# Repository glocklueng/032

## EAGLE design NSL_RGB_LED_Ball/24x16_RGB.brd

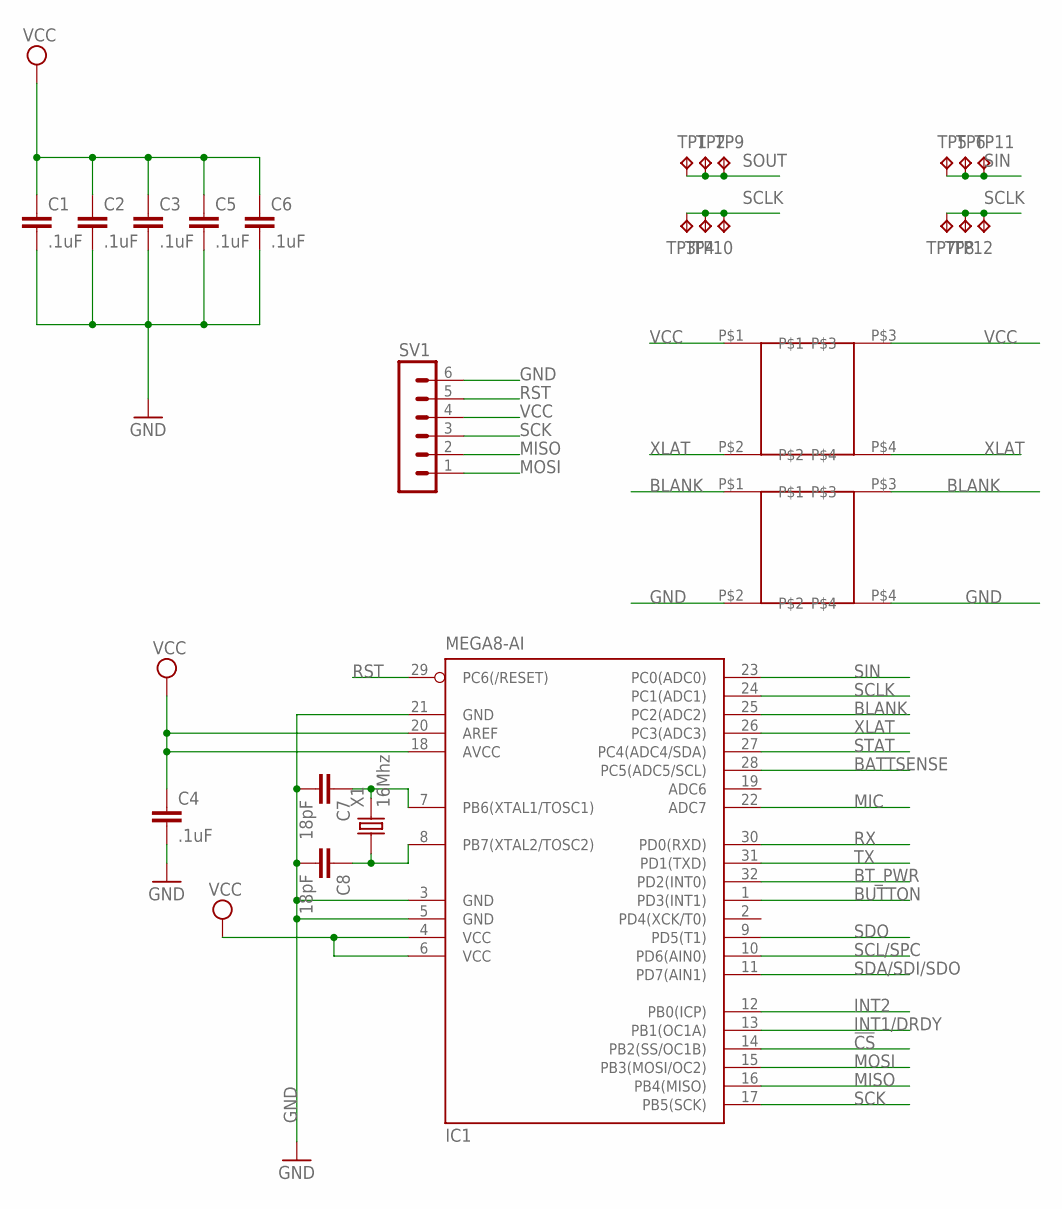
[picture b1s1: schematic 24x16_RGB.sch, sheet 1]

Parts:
C1, C2, C3, C4, C5, C6: .1uF; 0805
C7, C8: 18pF; 0805
IC1: MEGA8-AI; TQFP32-08
SLOT1, SLOT2: SLOT
SV1: MA06-1
TP1, TP2, TP3, TP4, TP5, TP6, TP7, TP8, TP9, TP10, TP11, TP12: TPTP20SQ; TP20SQ
X1: 16Mhz; 5032

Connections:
!CS: IC1.14 (PB2(SS/OC1B)); also elsewhere on the board
BATTSENSE: IC1.28 (PC5(ADC5/SCL)); also elsewhere on the board
BLANK: IC1.25 (PC2(ADC2)), SLOT2.P$1, SLOT2.P$3; also elsewhere on the board
BT_PWR: IC1.32 (PD2(INT0)); also elsewhere on the board
BUTTON: IC1.1 (PD3(INT1)); also elsewhere on the board
GND: C1.2, C2.2, C3.2, C4.2, C5.2, C6.2, C7.2, C8.2, IC1.3 (GND), IC1.5 (GND), IC1.21 (GND), SLOT2.P$2, SLOT2.P$4, SV1.6; also elsewhere on the board
INT1/DRDY: IC1.13 (PB1(OC1A)); also elsewhere on the board
INT2: IC1.12 (PB0(ICP)); also elsewhere on the board
MIC: IC1.22 (ADC7); also elsewhere on the board
MISO: IC1.16 (PB4(MISO)), SV1.2
MOSI: IC1.15 (PB3(MOSI/OC2)), SV1.1
unnamed: C7.1, IC1.7 (PB6(XTAL1/TOSC1)), X1.2
unnamed: C8.1, IC1.8 (PB7(XTAL2/TOSC2)), X1.1
RST: IC1.29 (PC6(/RESET)), SV1.5; also elsewhere on the board
RX: IC1.30 (PD0(RXD)); also elsewhere on the board
SCK: IC1.17 (PB5(SCK)), SV1.3
SCL/SPC: IC1.10 (PD6(AIN0)); also elsewhere on the board
SCLK: IC1.24 (PC1(ADC1)), TP3.TP, TP4.TP, TP7.TP, TP8.TP, TP10.TP, TP12.TP; also elsewhere on the board
SDA/SDI/SDO: IC1.11 (PD7(AIN1)); also elsewhere on the board
SDO: IC1.9 (PD5(T1)); also elsewhere on the board
SIN: IC1.23 (PC0(ADC0)), TP5.TP, TP6.TP, TP11.TP; also elsewhere on the board
SOUT: TP1.TP, TP2.TP, TP9.TP; also elsewhere on the board
STAT: IC1.27 (PC4(ADC4/SDA)); also elsewhere on the board
TX: IC1.31 (PD1(TXD)); also elsewhere on the board
VCC: C1.1, C2.1, C3.1, C4.1, C5.1, C6.1, IC1.4 (VCC), IC1.6 (VCC), IC1.18 (AVCC), IC1.20 (AREF), SLOT1.P$1, SLOT1.P$3, SV1.4; also elsewhere on the board
XLAT: IC1.26 (PC3(ADC3)), SLOT1.P$2, SLOT1.P$4; also elsewhere on the board

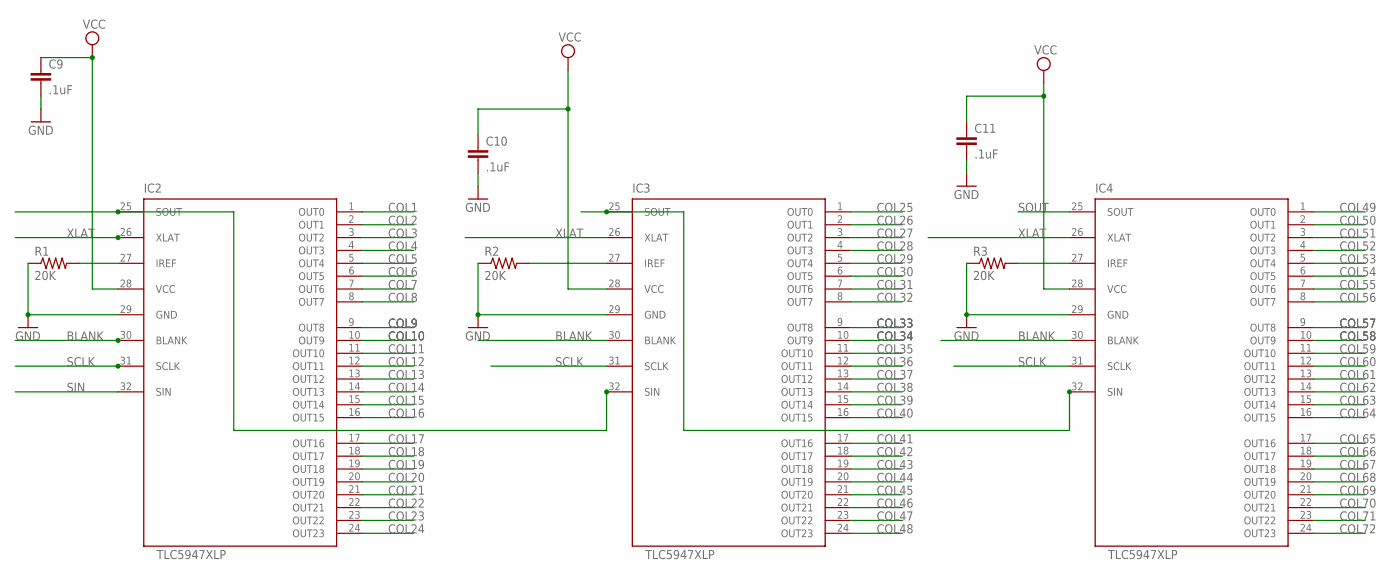
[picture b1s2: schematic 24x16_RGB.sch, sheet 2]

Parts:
C9, C10, C11: .1uF; 0805
IC2, IC3, IC4: TLC5947XLP; QFN32_XLP
R1, R2, R3: 20K; 0805

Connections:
BLANK: IC2.30 (BLANK), IC3.30 (BLANK), IC4.30 (BLANK); also elsewhere on the board
COL1: IC2.1 (OUT0); also elsewhere on the board
COL2: IC2.2 (OUT1); also elsewhere on the board
COL3: IC2.3 (OUT2); also elsewhere on the board
COL4: IC2.4 (OUT3); also elsewhere on the board
COL5: IC2.5 (OUT4); also elsewhere on the board
COL6: IC2.6 (OUT5); also elsewhere on the board
COL7: IC2.7 (OUT6); also elsewhere on the board
COL8: IC2.8 (OUT7); also elsewhere on the board
COL9: IC2.9 (OUT8); also elsewhere on the board
COL10: IC2.10 (OUT9); also elsewhere on the board
COL11: IC2.11 (OUT10); also elsewhere on the board
COL12: IC2.12 (OUT11); also elsewhere on the board
COL13: IC2.13 (OUT12); also elsewhere on the board
COL14: IC2.14 (OUT13); also elsewhere on the board
COL15: IC2.15 (OUT14); also elsewhere on the board
COL16: IC2.16 (OUT15); also elsewhere on the board
COL17: IC2.17 (OUT16); also elsewhere on the board
COL18: IC2.18 (OUT17); also elsewhere on the board
COL19: IC2.19 (OUT18); also elsewhere on the board
COL20: IC2.20 (OUT19); also elsewhere on the board
COL21: IC2.21 (OUT20); also elsewhere on the board
COL22: IC2.22 (OUT21); also elsewhere on the board
COL23: IC2.23 (OUT22); also elsewhere on the board
COL24: IC2.24 (OUT23); also elsewhere on the board
COL25: IC3.1 (OUT0); also elsewhere on the board
COL26: IC3.2 (OUT1); also elsewhere on the board
COL27: IC3.3 (OUT2); also elsewhere on the board
COL28: IC3.4 (OUT3); also elsewhere on the board
COL29: IC3.5 (OUT4); also elsewhere on the board
COL30: IC3.6 (OUT5); also elsewhere on the board
COL31: IC3.7 (OUT6); also elsewhere on the board
COL32: IC3.8 (OUT7); also elsewhere on the board
COL33: IC3.9 (OUT8); also elsewhere on the board
COL34: IC3.10 (OUT9); also elsewhere on the board
COL35: IC3.11 (OUT10); also elsewhere on the board
COL36: IC3.12 (OUT11); also elsewhere on the board
COL37: IC3.13 (OUT12); also elsewhere on the board
COL38: IC3.14 (OUT13); also elsewhere on the board
COL39: IC3.15 (OUT14); also elsewhere on the board
COL40: IC3.16 (OUT15); also elsewhere on the board
COL41: IC3.17 (OUT16); also elsewhere on the board
COL42: IC3.18 (OUT17); also elsewhere on the board
COL43: IC3.19 (OUT18); also elsewhere on the board
COL44: IC3.20 (OUT19); also elsewhere on the board
COL45: IC3.21 (OUT20); also elsewhere on the board
COL46: IC3.22 (OUT21); also elsewhere on the board
COL47: IC3.23 (OUT22); also elsewhere on the board
COL48: IC3.24 (OUT23); also elsewhere on the board
COL49: IC4.1 (OUT0); also elsewhere on the board
COL50: IC4.2 (OUT1); also elsewhere on the board
COL51: IC4.3 (OUT2); also elsewhere on the board
COL52: IC4.4 (OUT3); also elsewhere on the board
COL53: IC4.5 (OUT4); also elsewhere on the board
COL54: IC4.6 (OUT5); also elsewhere on the board
COL55: IC4.7 (OUT6); also elsewhere on the board
COL56: IC4.8 (OUT7); also elsewhere on the board
COL57: IC4.9 (OUT8); also elsewhere on the board
COL58: IC4.10 (OUT9); also elsewhere on the board
COL59: IC4.11 (OUT10); also elsewhere on the board
COL60: IC4.12 (OUT11); also elsewhere on the board
COL61: IC4.13 (OUT12); also elsewhere on the board
COL62: IC4.14 (OUT13); also elsewhere on the board
COL63: IC4.15 (OUT14); also elsewhere on the board
COL64: IC4.16 (OUT15); also elsewhere on the board
COL65: IC4.17 (OUT16); also elsewhere on the board
COL66: IC4.18 (OUT17); also elsewhere on the board
COL67: IC4.19 (OUT18); also elsewhere on the board
COL68: IC4.20 (OUT19); also elsewhere on the board
COL69: IC4.21 (OUT20); also elsewhere on the board
COL70: IC4.22 (OUT21); also elsewhere on the board
COL71: IC4.23 (OUT22); also elsewhere on the board
COL72: IC4.24 (OUT23); also elsewhere on the board
GND: C9.2, C10.2, C11.2, IC2.29 (GND), IC3.29 (GND), IC4.29 (GND), R1.1, R2.1, R3.1; also elsewhere on the board
HOLE: IC2.27 (IREF), R1.2
unnamed: IC3.27 (IREF), R2.2
unnamed: IC2.25 (SOUT), IC3.32 (SIN)
unnamed: IC4.27 (IREF), R3.2
unnamed: IC3.25 (SOUT), IC4.32 (SIN)
SCLK: IC2.31 (SCLK), IC3.31 (SCLK), IC4.31 (SCLK); also elsewhere on the board
SIN: IC2.32 (SIN); also elsewhere on the board
SOUT: IC4.25 (SOUT); also elsewhere on the board
VCC: C9.1, C10.1, C11.1, IC2.28 (VCC), IC3.28 (VCC), IC4.28 (VCC); also elsewhere on the board
XLAT: IC2.26 (XLAT), IC3.26 (XLAT), IC4.26 (XLAT); also elsewhere on the board

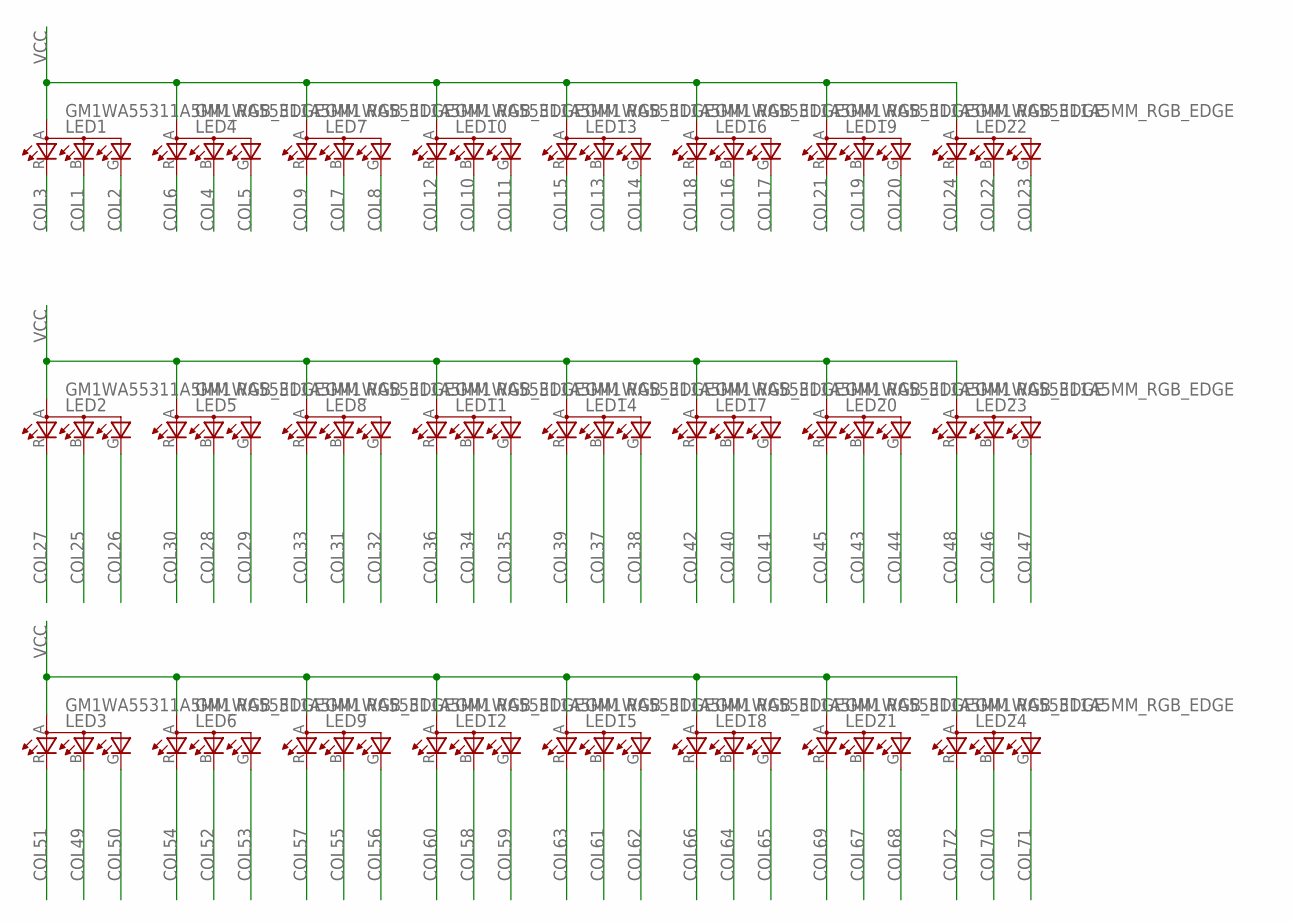
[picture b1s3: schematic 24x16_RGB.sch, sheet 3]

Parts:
LED1, LED2, LED3, LED4, LED5, LED6, LED7, LED8, LED9, LED10, LED11, LED12, LED13, LED14, LED15, LED16, LED17, LED18, LED19, LED20, LED21, LED22, LED23, LED24: GM1WA55311A5MM_RGB_EDGE; LED5MM_RGB_EDGE

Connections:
COL1: LED1.B (CBLUE); also elsewhere on the board
COL2: LED1.G (CGREEN); also elsewhere on the board
COL3: LED1.R (CRED); also elsewhere on the board
COL4: LED4.B (CBLUE); also elsewhere on the board
COL5: LED4.G (CGREEN); also elsewhere on the board
COL6: LED4.R (CRED); also elsewhere on the board
COL7: LED7.B (CBLUE); also elsewhere on the board
COL8: LED7.G (CGREEN); also elsewhere on the board
COL9: LED7.R (CRED); also elsewhere on the board
COL10: LED10.B (CBLUE); also elsewhere on the board
COL11: LED10.G (CGREEN); also elsewhere on the board
COL12: LED10.R (CRED); also elsewhere on the board
COL13: LED13.B (CBLUE); also elsewhere on the board
COL14: LED13.G (CGREEN); also elsewhere on the board
COL15: LED13.R (CRED); also elsewhere on the board
COL16: LED16.B (CBLUE); also elsewhere on the board
COL17: LED16.G (CGREEN); also elsewhere on the board
COL18: LED16.R (CRED); also elsewhere on the board
COL19: LED19.B (CBLUE); also elsewhere on the board
COL20: LED19.G (CGREEN); also elsewhere on the board
COL21: LED19.R (CRED); also elsewhere on the board
COL22: LED22.B (CBLUE); also elsewhere on the board
COL23: LED22.G (CGREEN); also elsewhere on the board
COL24: LED22.R (CRED); also elsewhere on the board
COL25: LED2.B (CBLUE); also elsewhere on the board
COL26: LED2.G (CGREEN); also elsewhere on the board
COL27: LED2.R (CRED); also elsewhere on the board
COL28: LED5.B (CBLUE); also elsewhere on the board
COL29: LED5.G (CGREEN); also elsewhere on the board
COL30: LED5.R (CRED); also elsewhere on the board
COL31: LED8.B (CBLUE); also elsewhere on the board
COL32: LED8.G (CGREEN); also elsewhere on the board
COL33: LED8.R (CRED); also elsewhere on the board
COL34: LED11.B (CBLUE); also elsewhere on the board
COL35: LED11.G (CGREEN); also elsewhere on the board
COL36: LED11.R (CRED); also elsewhere on the board
COL37: LED14.B (CBLUE); also elsewhere on the board
COL38: LED14.G (CGREEN); also elsewhere on the board
COL39: LED14.R (CRED); also elsewhere on the board
COL40: LED17.B (CBLUE); also elsewhere on the board
COL41: LED17.G (CGREEN); also elsewhere on the board
COL42: LED17.R (CRED); also elsewhere on the board
COL43: LED20.B (CBLUE); also elsewhere on the board
COL44: LED20.G (CGREEN); also elsewhere on the board
COL45: LED20.R (CRED); also elsewhere on the board
COL46: LED23.B (CBLUE); also elsewhere on the board
COL47: LED23.G (CGREEN); also elsewhere on the board
COL48: LED23.R (CRED); also elsewhere on the board
COL49: LED3.B (CBLUE); also elsewhere on the board
COL50: LED3.G (CGREEN); also elsewhere on the board
COL51: LED3.R (CRED); also elsewhere on the board
COL52: LED6.B (CBLUE); also elsewhere on the board
COL53: LED6.G (CGREEN); also elsewhere on the board
COL54: LED6.R (CRED); also elsewhere on the board
COL55: LED9.B (CBLUE); also elsewhere on the board
COL56: LED9.G (CGREEN); also elsewhere on the board
COL57: LED9.R (CRED); also elsewhere on the board
COL58: LED12.B (CBLUE); also elsewhere on the board
COL59: LED12.G (CGREEN); also elsewhere on the board
COL60: LED12.R (CRED); also elsewhere on the board
COL61: LED15.B (CBLUE); also elsewhere on the board
COL62: LED15.G (CGREEN); also elsewhere on the board
COL63: LED15.R (CRED); also elsewhere on the board
COL64: LED18.B (CBLUE); also elsewhere on the board
COL65: LED18.G (CGREEN); also elsewhere on the board
COL66: LED18.R (CRED); also elsewhere on the board
COL67: LED21.B (CBLUE); also elsewhere on the board
COL68: LED21.G (CGREEN); also elsewhere on the board
COL69: LED21.R (CRED); also elsewhere on the board
COL70: LED24.B (CBLUE); also elsewhere on the board
COL71: LED24.G (CGREEN); also elsewhere on the board
COL72: LED24.R (CRED); also elsewhere on the board
VCC: LED1.A, LED2.A, LED3.A, LED4.A, LED5.A, LED6.A, LED7.A, LED8.A, LED9.A, LED10.A, LED11.A, LED12.A, LED13.A, LED14.A, LED15.A, LED16.A, LED17.A, LED18.A, LED19.A, LED20.A, LED21.A, LED22.A, LED23.A, LED24.A; also elsewhere on the board

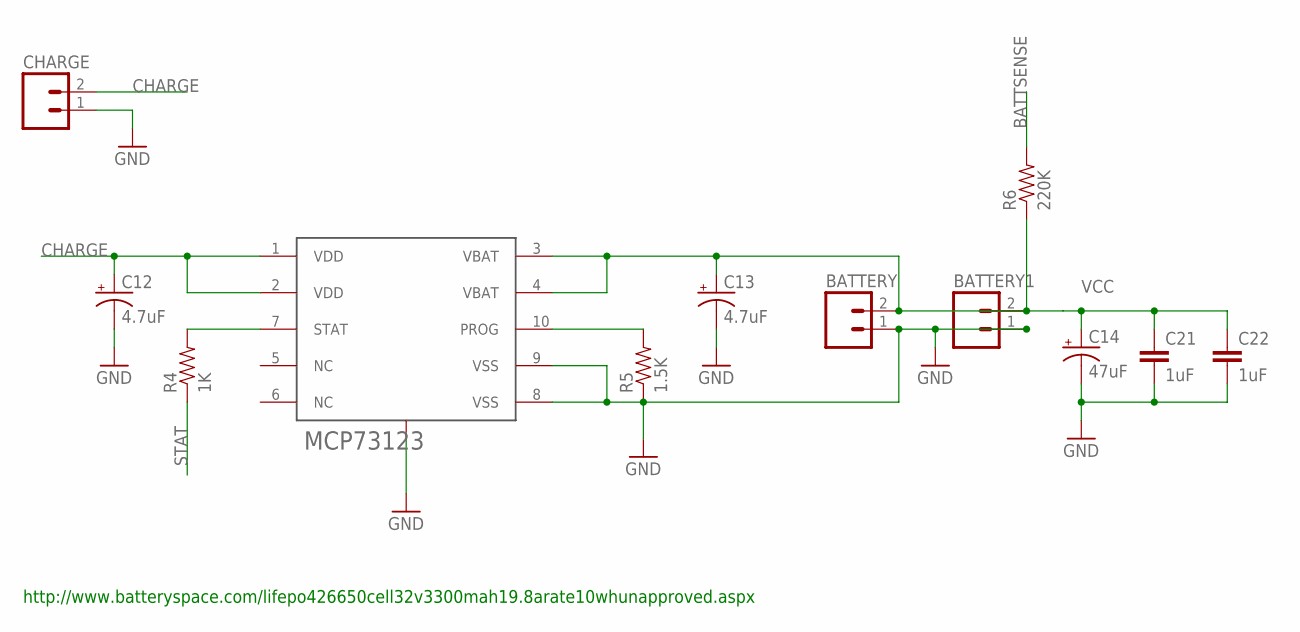
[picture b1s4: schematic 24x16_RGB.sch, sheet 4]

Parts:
BATTERY, BATTERY1: M02PTH; 1X02
C12, C13: 4.7uF; EIA3528
C14: 47uF; EIA3528
C21, C22: 1uF; 0805
CHARGE: M02PTH; 1X02
IC5: MCP73123; DFN10_3X3
R4: 1K; 0805
R5: 1.5K; 0805
R6: 220K; 0805

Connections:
BATTSENSE: R6.2; also elsewhere on the board
CHARGE: C12.A (+), CHARGE.2, IC5.1 (VDD), IC5.2 (VDD)
GND: BATTERY.1, BATTERY1.1, C12.C (-), C13.C (-), C14.C (-), C21.2, C22.2, CHARGE.1, IC5.8 (VSS), IC5.9 (VSS), IC5.EXP (GND), R5.1; also elsewhere on the board
unnamed: IC5.7 (STAT), R4.2
unnamed: IC5.10 (PROG), R5.2
STAT: R4.1; also elsewhere on the board
VCC: BATTERY.2, BATTERY1.2, C13.A (+), C14.A (+), C21.1, C22.1, IC5.3 (VBAT), IC5.4 (VBAT), R6.1; also elsewhere on the board

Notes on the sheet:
http://www.batteryspace.com/lifepo426650cell32v3300mah19.8arate10whunapproved.aspx

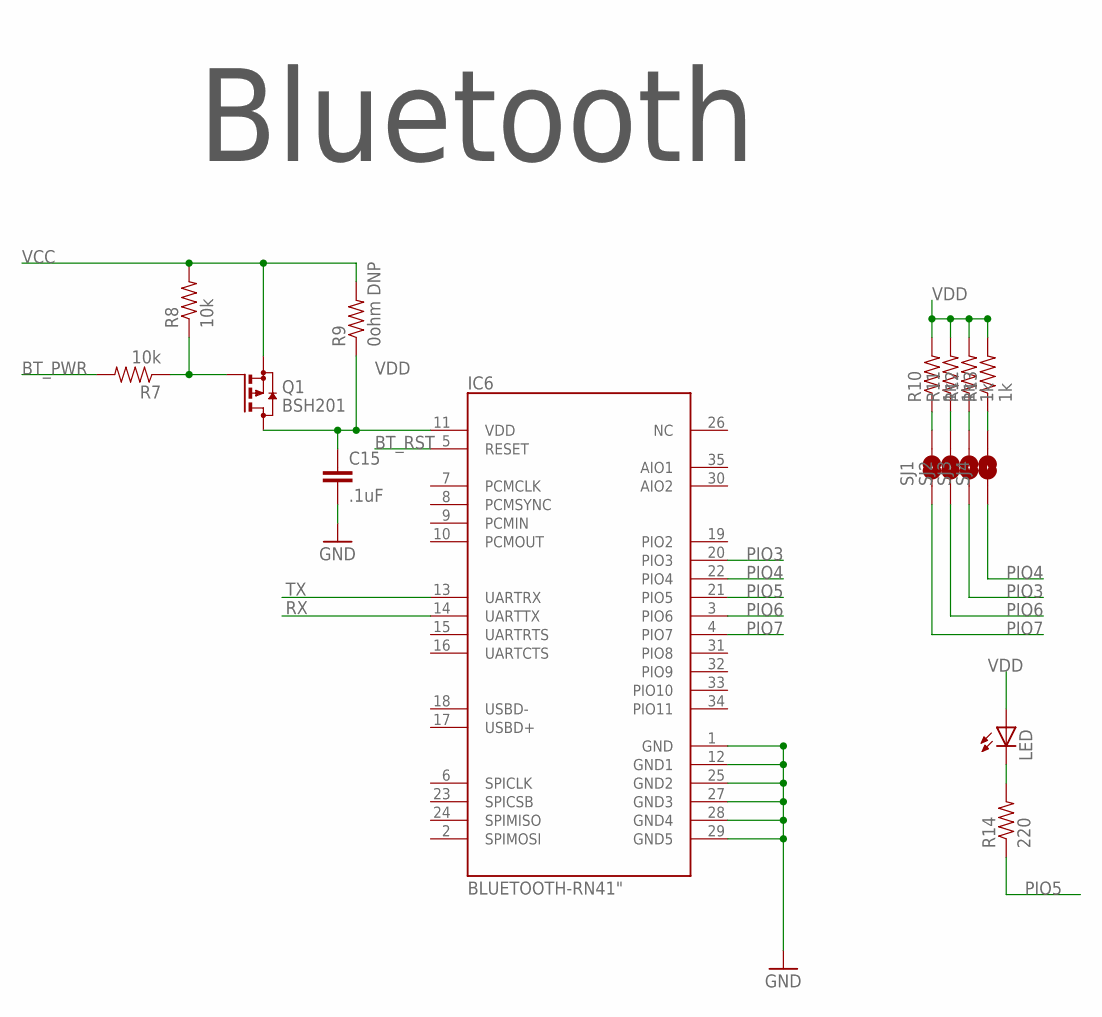
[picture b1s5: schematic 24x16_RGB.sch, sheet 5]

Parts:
C15: .1uF; 0805
IC6: BLUETOOTH-RN41"; RN41
LED: LEDCHIP-LED0603; CHIP-LED0603
Q1: BSH201; SOT23
R7, R8: 10k; 0805
R9: 0ohm DNP; 0805
R10, R11, R12, R13: 1k; 0805
R14: 220; 0805
SJ1, SJ2, SJ3, SJ4: SOLDERJUMPERNO; SJ_2S-NO

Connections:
BT_PWR: R7.2; also elsewhere on the board
BT_RST: IC6.5 (RESET); also elsewhere on the board
GND: C15.2, IC6.1 (GND), IC6.12 (GND1), IC6.25 (GND2), IC6.27 (GND3), IC6.28 (GND4), IC6.29 (GND5); also elsewhere on the board
unnamed: LED.C, R14.2
unnamed: R10.1, SJ1.2
unnamed: Q1.1 (G), R7.1, R8.1
unnamed: R12.1, SJ3.2
unnamed: R11.1, SJ2.2
unnamed: R13.1, SJ4.2
PIO3: IC6.20 (PIO3), SJ3.1
PIO4: IC6.22 (PIO4), SJ4.1
PIO5: IC6.21 (PIO5), R14.1
PIO6: IC6.3 (PIO6), SJ2.1
PIO7: IC6.4 (PIO7), SJ1.1
RX: IC6.14 (UARTTX); also elsewhere on the board
TX: IC6.13 (UARTRX); also elsewhere on the board
VCC: Q1.2 (S), R8.2, R9.2; also elsewhere on the board
VDD: C15.1, IC6.11 (VDD), LED.A, Q1.3 (D), R9.1, R10.2, R11.2, R12.2, R13.2

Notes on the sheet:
Bluetooth

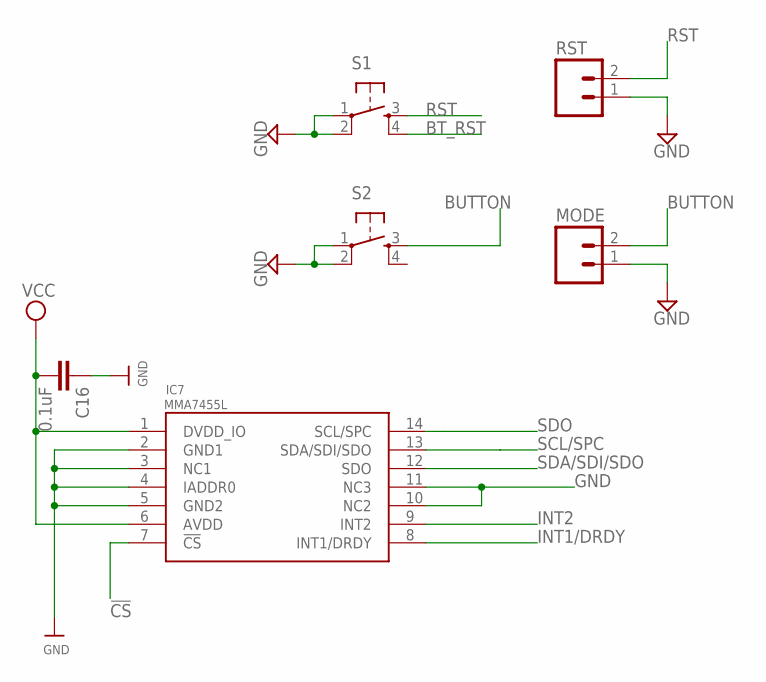
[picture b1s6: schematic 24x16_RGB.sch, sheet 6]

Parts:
C16: 0.1uF; 0805
IC7: MMA7455L; LGA-14
MODE: M02PTH; 1X02
RST: M02PTH; 1X02
S1, S2: TAC_SWITCHSMD; TACTILE_SWITCH_SMD

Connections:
!CS: IC7.7 (!CS); also elsewhere on the board
BT_RST: S1.4; also elsewhere on the board
BUTTON: MODE.2, S2.3; also elsewhere on the board
GND: C16.1, IC7.2 (GND1), IC7.3 (NC1), IC7.4 (IADDR0), IC7.5 (GND2), IC7.10 (NC2), IC7.11 (NC3), MODE.1, RST.1, S1.1, S1.2, S2.1, S2.2; also elsewhere on the board
INT1/DRDY: IC7.8 (INT1/DRDY); also elsewhere on the board
INT2: IC7.9 (INT2); also elsewhere on the board
RST: RST.2, S1.3; also elsewhere on the board
SCL/SPC: IC7.13 (SDA/SDI/SDO); also elsewhere on the board
SDA/SDI/SDO: IC7.12 (SDO); also elsewhere on the board
SDO: IC7.14 (SCL/SPC); also elsewhere on the board
VCC: C16.2, IC7.1 (DVDD_IO), IC7.6 (AVDD); also elsewhere on the board

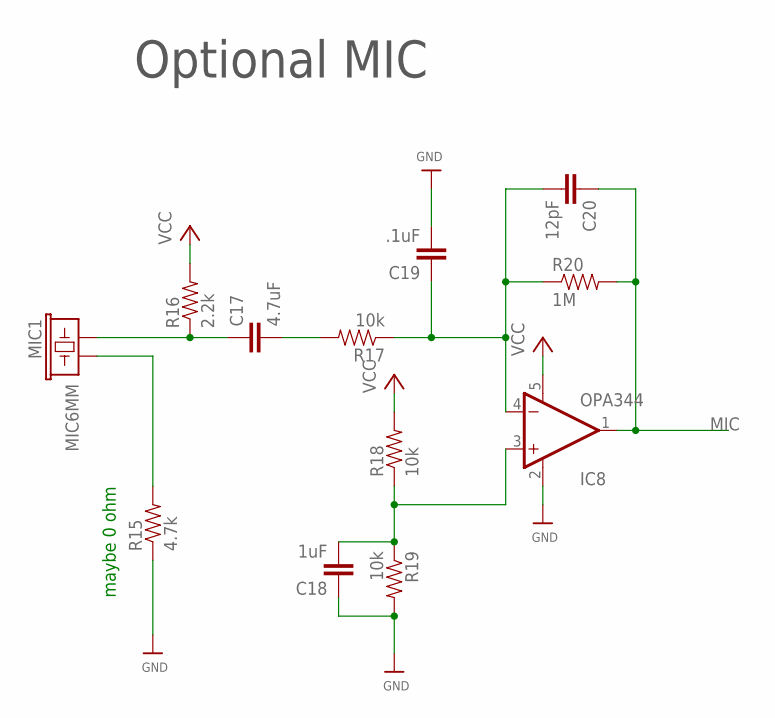
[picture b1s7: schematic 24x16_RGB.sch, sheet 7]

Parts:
C17: 4.7uF; 0805
C18: 1uF; 0805
C19: .1uF; 0805
C20: 12pF; 0805
IC8: OPA344; SOT23-5
MIC1: MIC6MM; MIC-6MM
R15: 4.7k; 0805
R16: 2.2k; 0805
R17, R18, R19: 10k; 0805
R20: 1M; 0805

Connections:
GND: C18.1, C19.2, IC8.2 (V-), R15.1, R19.2; also elsewhere on the board
MIC: C20.1, IC8.1 (OUT), R20.2; also elsewhere on the board
unnamed: C17.2, R17.2
unnamed: C17.1, MIC1.1, R16.1
unnamed: C18.2, IC8.3 (+IN), R18.1, R19.1
unnamed: C19.1, C20.2, IC8.4 (-IN), R17.1, R20.1
unnamed: MIC1.2, R15.2
VCC: IC8.5 (V+), R16.2, R18.2; also elsewhere on the board

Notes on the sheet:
Optional MIC
maybe 0 ohm

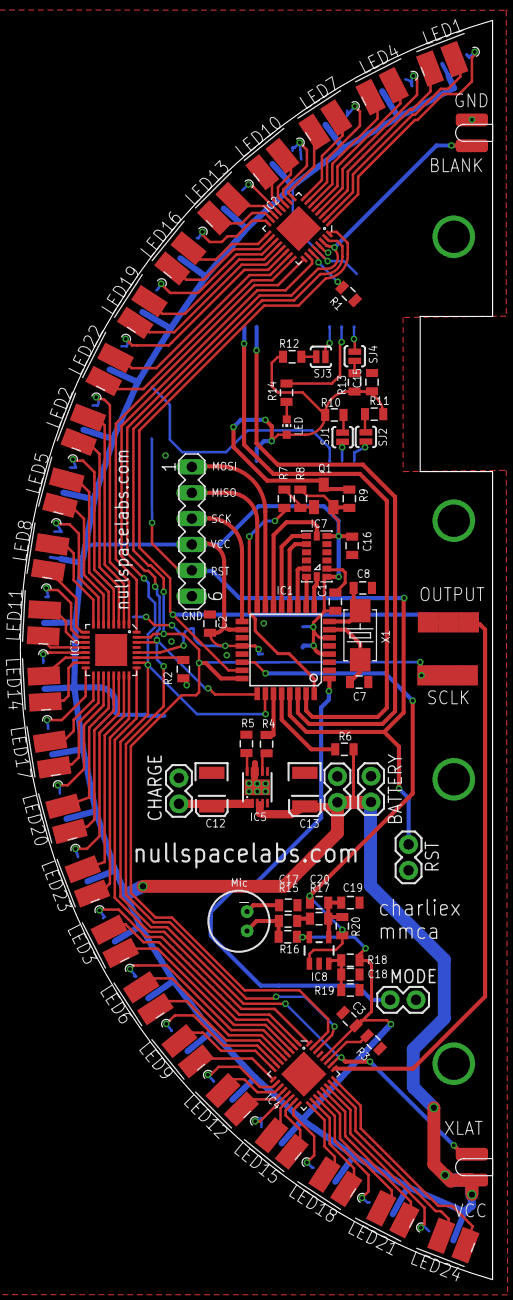
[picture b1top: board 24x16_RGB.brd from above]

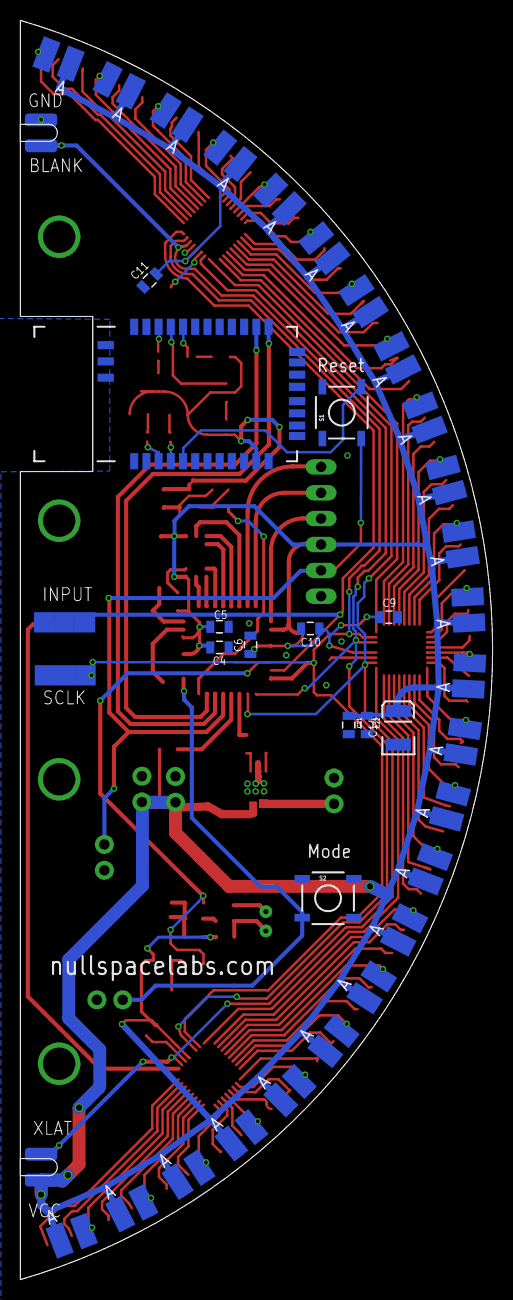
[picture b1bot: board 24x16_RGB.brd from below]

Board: 2 copper layers, 46.4 x 123.7 mm, 104 parts (18 on the bottom side), 124 nets.

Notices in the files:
parts and their libraries:
SparkFun-Connectors: Licensing: CC v3.0 Share-Alike You are welcome to use this library for commercial purposes.
